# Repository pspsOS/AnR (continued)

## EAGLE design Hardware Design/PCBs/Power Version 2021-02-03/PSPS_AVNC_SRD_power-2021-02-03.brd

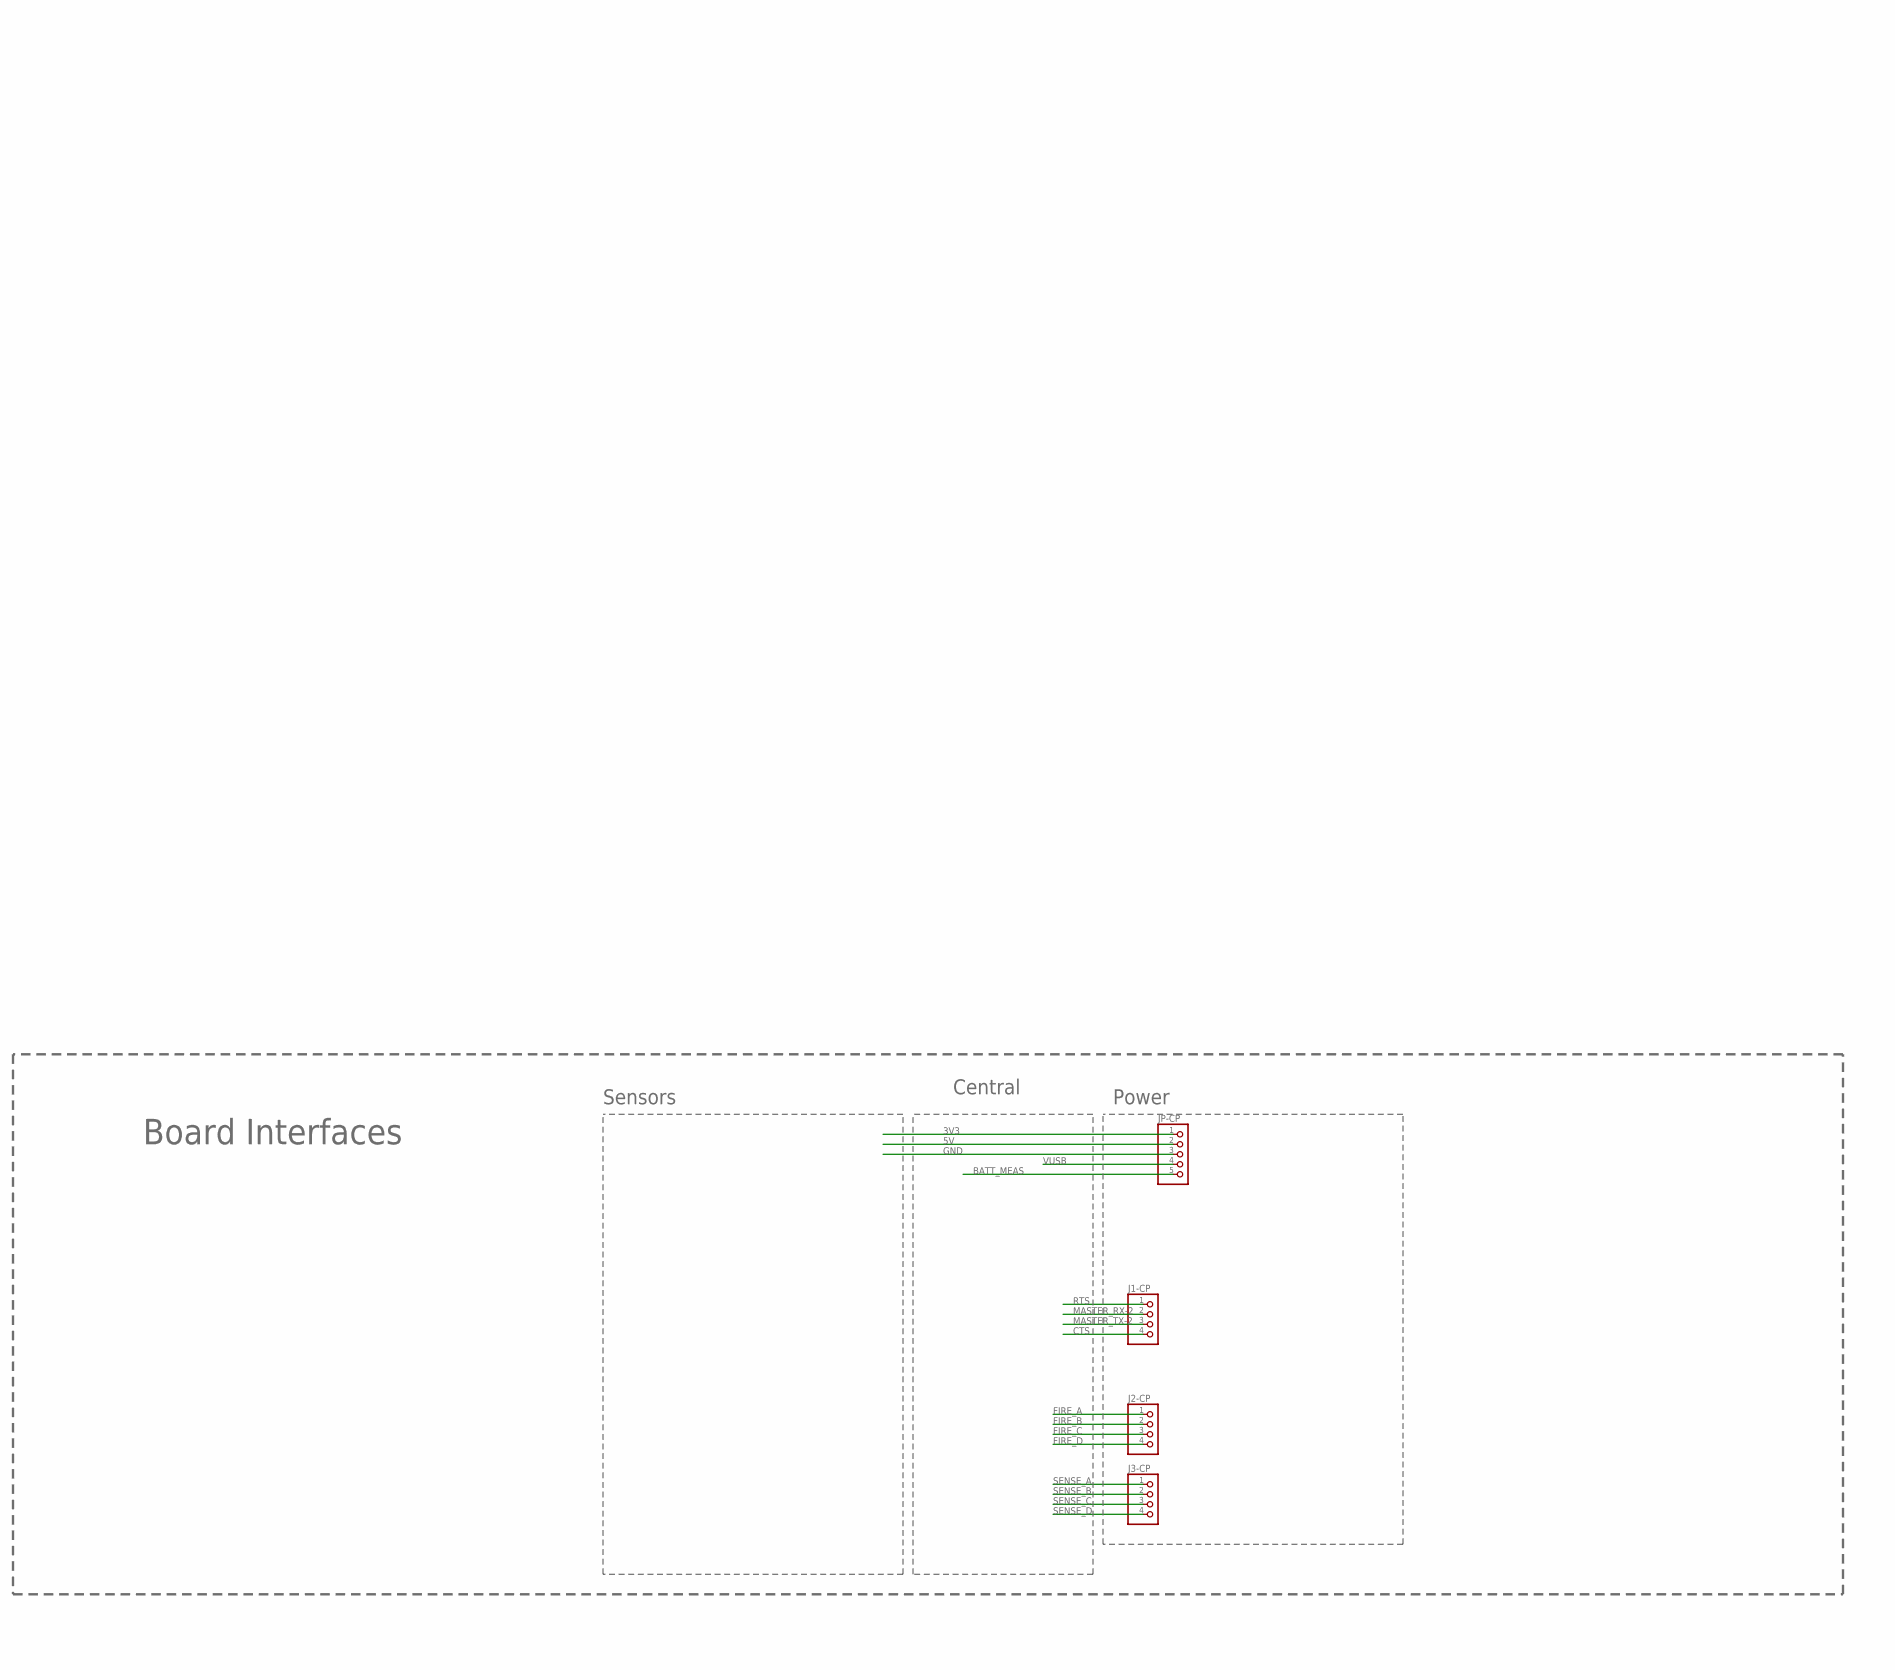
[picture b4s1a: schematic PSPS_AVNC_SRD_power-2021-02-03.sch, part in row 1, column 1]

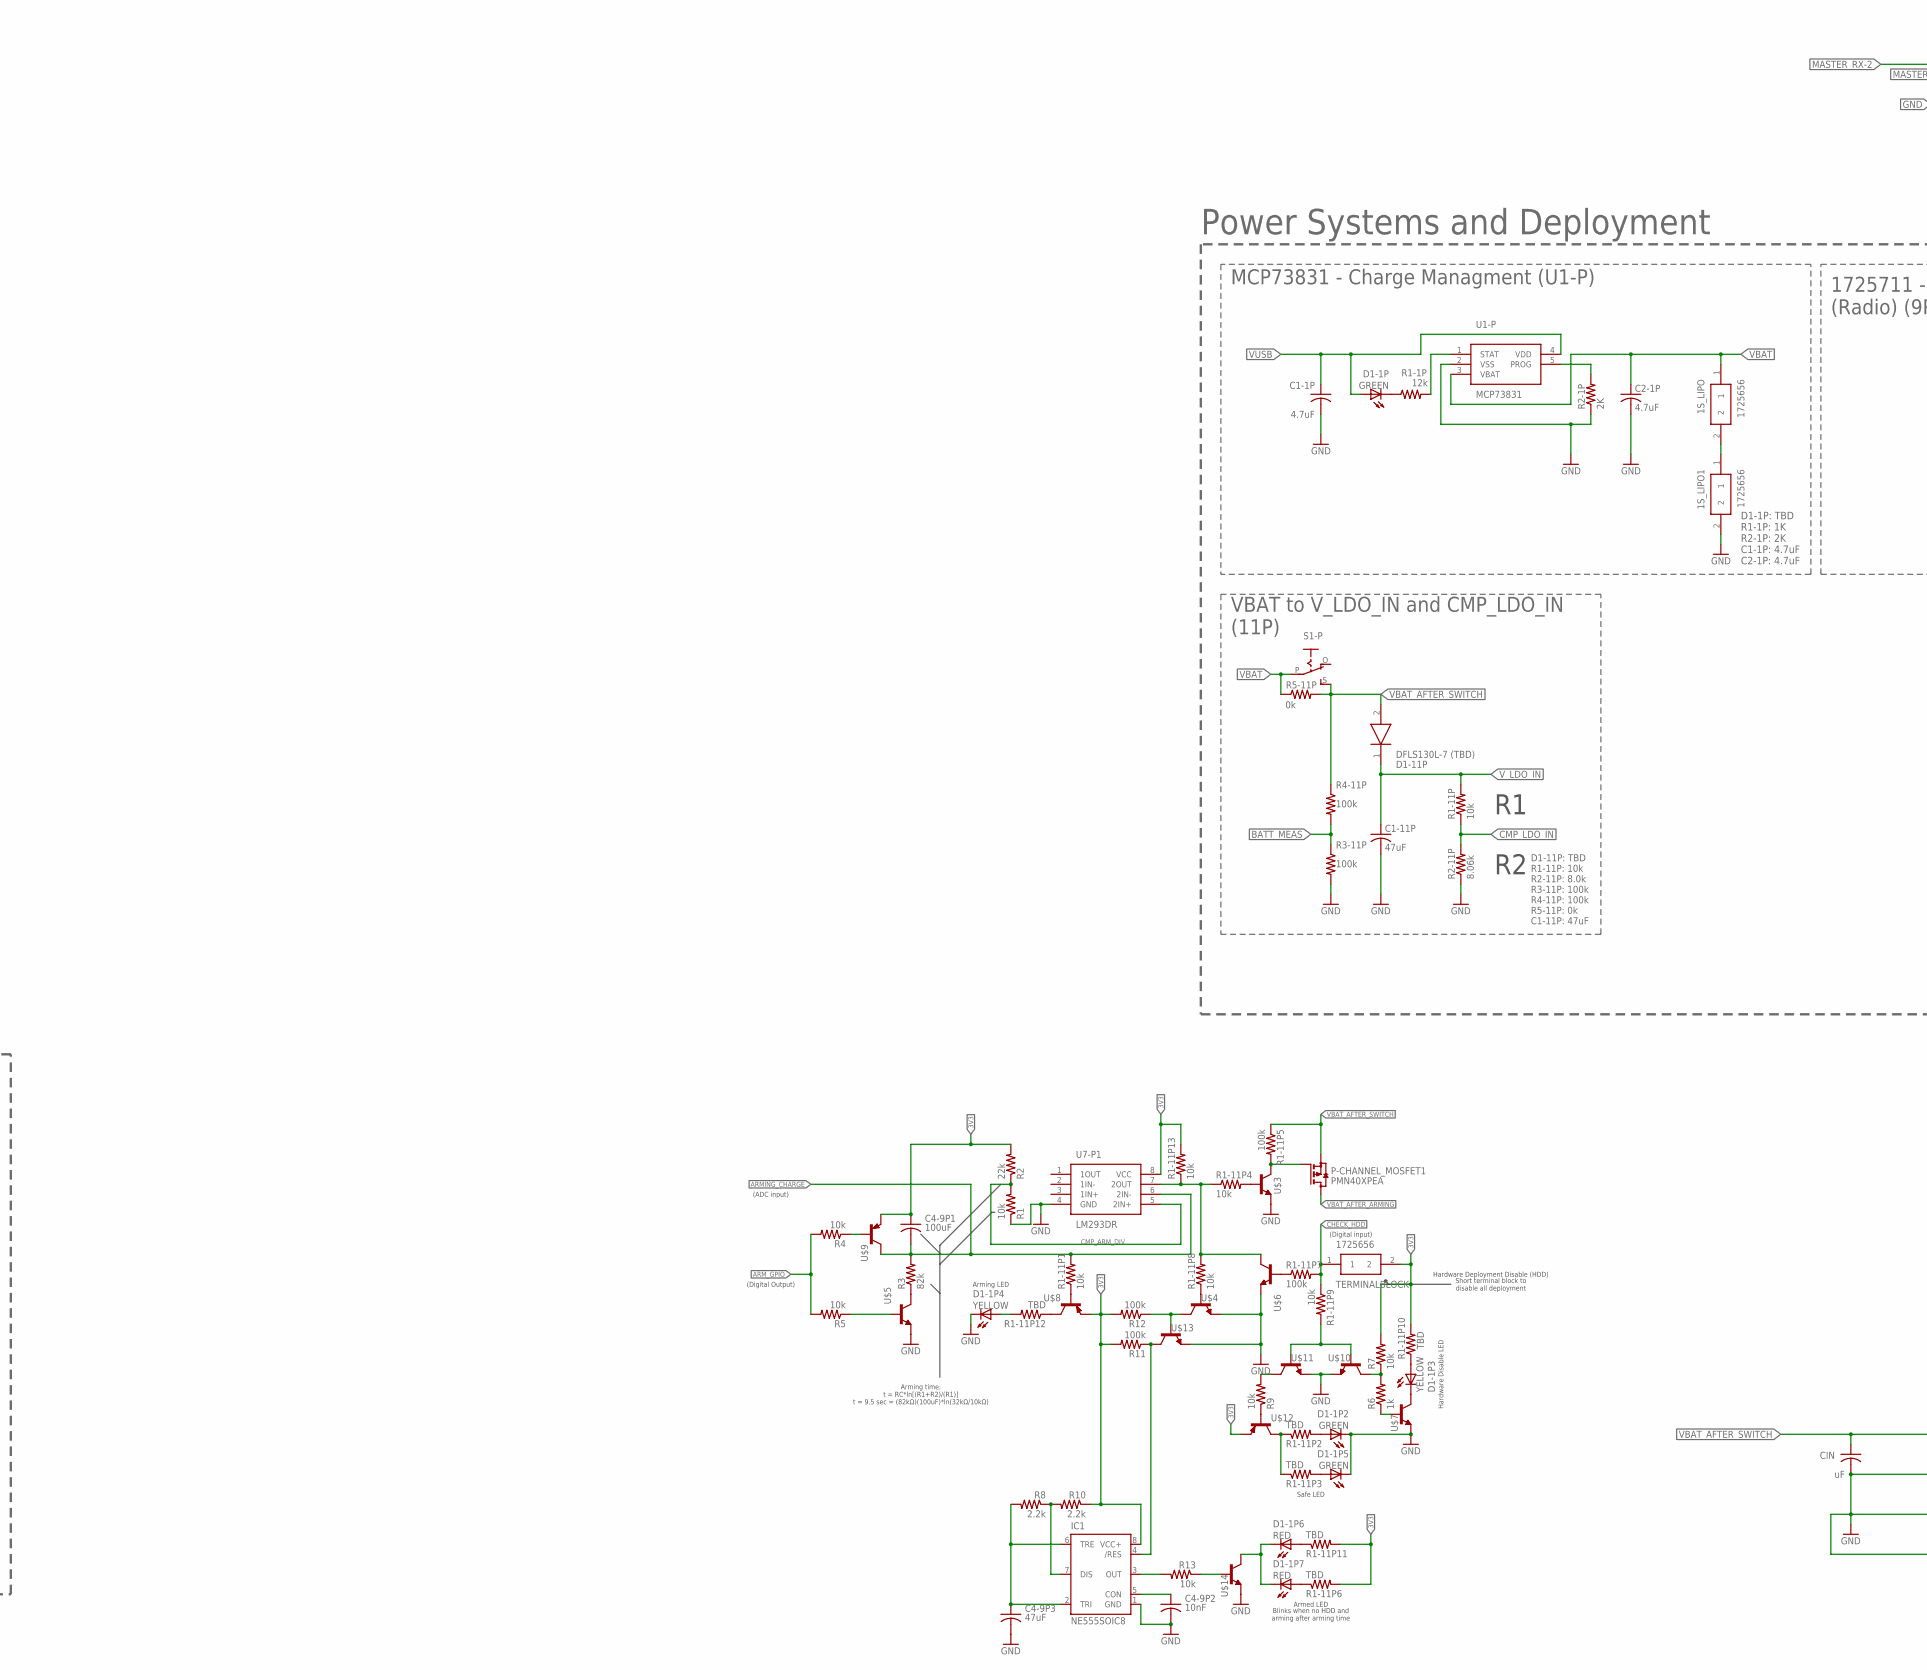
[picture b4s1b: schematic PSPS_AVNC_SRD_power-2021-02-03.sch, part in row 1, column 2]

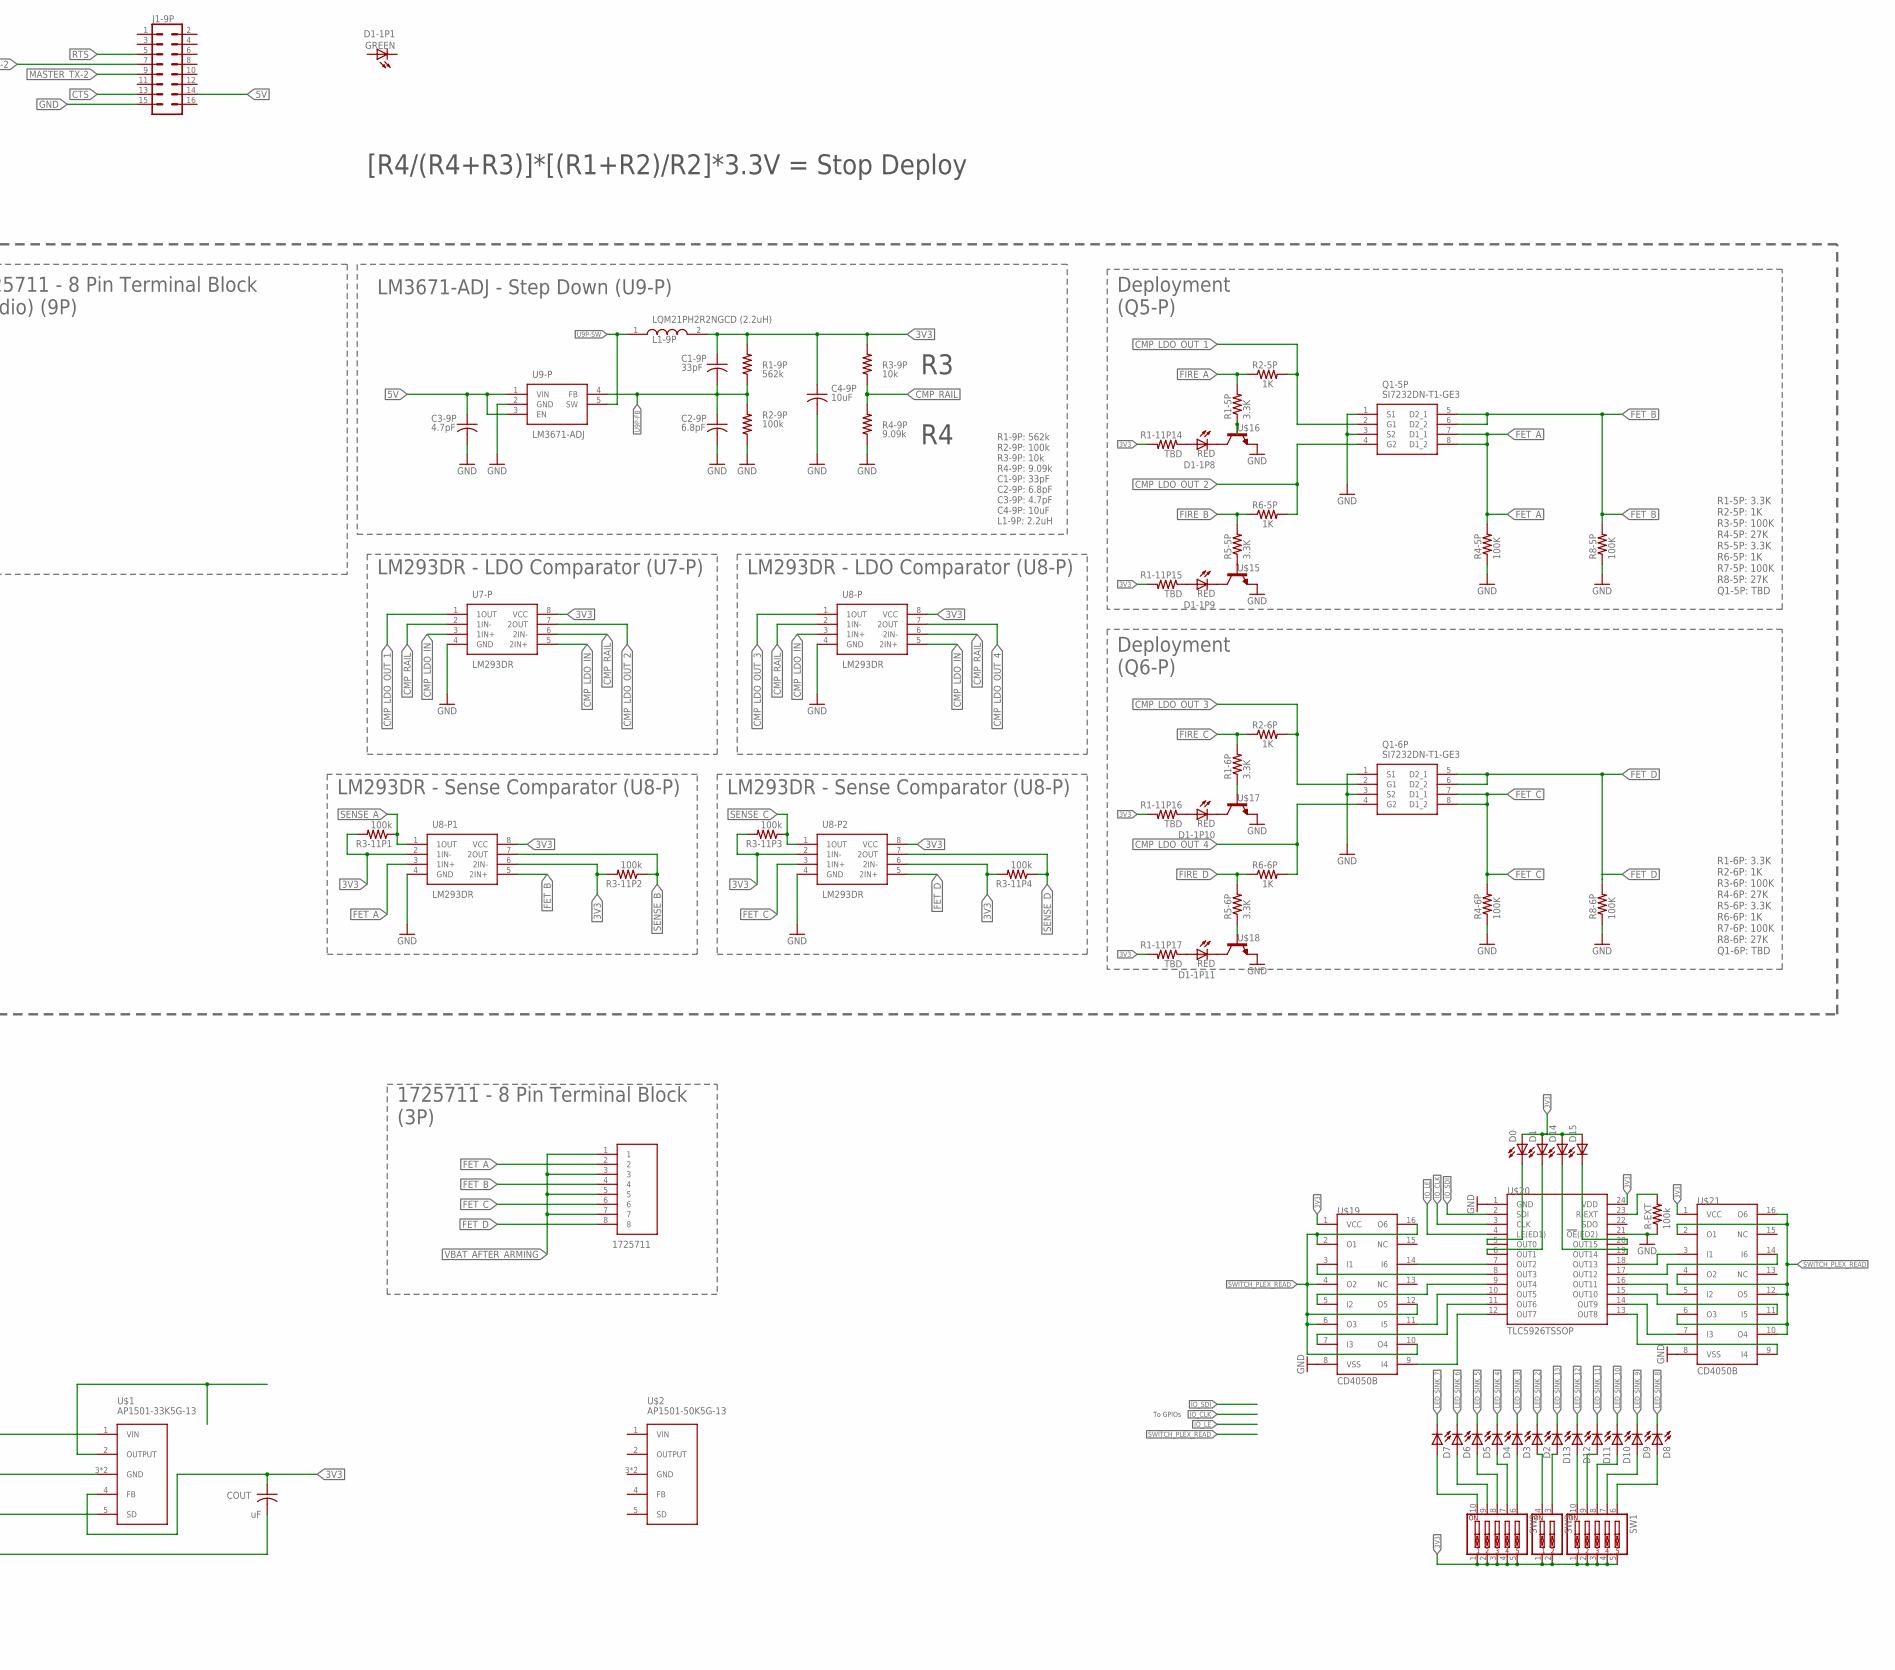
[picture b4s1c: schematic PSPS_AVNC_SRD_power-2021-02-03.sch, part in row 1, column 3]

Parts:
1S_LIPO, 1S_LIPO1: 1725656
C1-1P, C2-1P: 4.7uF; C0805
C1-9P: 33pF; C0805
C1-11P, C4-9P3: 47uF; C0805
C2-9P: 6.8pF; C0805
C3-9P: 4.7pF; C0805
C4-9P: 10uF; C0805
C4-9P1: 100uF; C0805
C4-9P2: 10nF; C0805
CIN: uF; C0805
COUT: uF; C0805
D0, D1, D2, D3, D4, D5, D6, D7, D8, D9, D10, D11, D12, D13, D14, D15: LEDCHIPLED_0805; CHIPLED_0805
D1-1P, D1-1P1, D1-1P2, D1-1P5: GREEN; CHIPLED_0805
D1-1P3, D1-1P4: YELLOW; CHIPLED_0805
D1-1P6, D1-1P7, D1-1P8, D1-1P9, D1-1P10, D1-1P11: RED; CHIPLED_0805
D1-11P: DFLS130L-7 (TBD); POWERDI_123
IC1: NE555SOIC8; SOIC127P599X175-8
J1-9P: CONN_08X2; 2X8
J1-CP, J2-CP, J3-CP: PINHD-1X4; 1X04
J2-P: 1725711
JP-CP: PINHD-1X5; 1X05
L1-9P: LQM21PH2R2NGCD (2.2uH); INDC2012X100N
P-CHANNEL_MOSFET1: PMN40XPEA
Q1-5P, Q1-6P: SI7232DN-T1-GE3; POWERPAK-1212-8
R1, R1-11P, R1-11P1, R1-11P4, R1-11P8, R1-11P9, R1-11P13, R3-9P, R4, R5, R7, R9, R13: 10k; R0805
R1-1P: 12k; R0805
R1-5P, R1-6P, R5-5P, R5-6P: 3.3K; M0805
R1-9P: 562k; R0805
R1-11P2, R1-11P3, R1-11P6, R1-11P10, R1-11P11, R1-11P12, R1-11P14, R1-11P15, R1-11P16, R1-11P17: TBD; R0805
R1-11P5, R1-11P7, R2-9P, R3-11P, R3-11P1, R3-11P2, R3-11P3, R3-11P4, R4-11P, R11, R12: 100k; R0805
R2: 22k; R0805
R2-1P: 2K; R0805
R2-5P, R2-6P, R6-5P, R6-6P: 1K; M0805
R2-11P: 8.06k; R0805
R3: 82k; R0805
R4-5P, R4-6P, R8-5P, R8-6P: 100K; M0805
R4-9P: 9.09k; R0805
R5-11P: 0k; R0805
R6: 1k; R0805
R8, R10: 2.2k; R0805
R-EXT: 100k; R0805
S1-P: EG1218S; EG1218
SW1, SW2: SW_DIP-5; EDG-05
SW3: SW_DIP-2; EDG-02
TERMINALBLOCK: 1725656
U1-P: MCP73831; SOT95P270X145-5N
U7-P, U7-P1, U8-P, U8-P1, U8-P2: LM293DR; SOIC127P600X175-8N
U9-P: LM3671-ADJ; SOT95P280X145-5N
U$1: AP1501-33K5G-13; TO185P1524X485-6N
U$2: AP1501-50K5G-13; TO185P1524X485-6N
U$3, U$4, U$5, U$6, U$7, U$10, U$11, U$13, U$14, U$15, U$16, U$17, U$18: NPN_TRANSISTOR; SOT23
U$8, U$9, U$12: PNP_TRANSISTOR; SOT23
U$19, U$21: CD4050B; SOIC127P600X175-16N
U$20: TLC5926TSSOP; SOP65P640X120-24N

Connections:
3V3: C1-9P.1, C4-9P.1, C4-9P1.1, COUT.1, D0.A, D1.A, D14.A, D15.A, IC1.8 (VCC+), JP-CP.1, L1-9P.2, R1-9P.2, R1-11P6.2, R1-11P10.2, R1-11P11.2, R1-11P13.2, R1-11P14.2, R1-11P15.2, R1-11P16.2, R1-11P17.2, R2.2, R3-9P.2, R3-11P1.2, R3-11P2.2, R3-11P3.2, R3-11P4.2, R7.2, R10.1, R11.2, R12.2, SW1.1, SW1.2, SW1.3, SW1.4, SW1.5, SW2.1, SW2.2, SW2.3, SW2.4, SW2.5, SW3.1, SW3.2, TERMINALBLOCK.2, U7-P.8 (VCC), U7-P1.8 (VCC), U8-P.8 (VCC), U8-P1.2 (1IN-), U8-P1.6 (2IN-), U8-P1.8 (VCC), U8-P2.2 (1IN-), U8-P2.6 (2IN-), U8-P2.8 (VCC), U$1.4 (FB), U$8.2 (E), U$9.2 (E), U$12.2 (E), U$19.1 (VCC), U$20.24 (VDD), U$21.1 (VCC)
5V: C3-9P.1, J1-9P.14, JP-CP.2, U9-P.1 (VIN), U9-P.3 (EN)
ARMING_CHARGE: C4-9P1.2, R1-11P1.2, R3.2, U7-P1.6 (2IN-), U$9.3 (C)
ARM_GPIO: R4.2, R5.2
BATT_MEAS: JP-CP.5, R3-11P.1, R4-11P.2
CHECK_HDD: R1-11P7.2, R1-11P9.1, TERMINALBLOCK.1
CMP_ARM_DIV: R1.2, R2.1, U7-P1.5 (2IN+)
CMP_LDO_IN: R1-11P.1, R2-11P.2, U7-P.3 (1IN+), U7-P.5 (2IN+), U8-P.3 (1IN+), U8-P.5 (2IN+)
CMP_LDO_OUT_1: Q1-5P.2 (G1), R2-5P.2, U7-P.1 (1OUT)
CMP_LDO_OUT_2: Q1-5P.4 (G2), R6-5P.2, U7-P.7 (2OUT)
CMP_LDO_OUT_3: Q1-6P.2 (G1), R2-6P.2, U8-P.1 (1OUT)
CMP_LDO_OUT_4: Q1-6P.4 (G2), R6-6P.2, U8-P.7 (2OUT)
CMP_RAIL: R3-9P.1, R4-9P.2, U7-P.2 (1IN-), U7-P.6 (2IN-), U8-P.2 (1IN-), U8-P.6 (2IN-)
CTS: J1-9P.13, J1-CP.4
D1-1P_R1-1P: D1-1P.C, R1-1P.1
FET_A: J2-P.2, Q1-5P.7 (D1_1), Q1-5P.8 (D1_2), R4-5P.2, U8-P1.3 (1IN+)
FET_B: J2-P.4, Q1-5P.5 (D2_1), Q1-5P.6 (D2_2), R8-5P.2, U8-P1.5 (2IN+)
FET_C: J2-P.6, Q1-6P.7 (D1_1), Q1-6P.8 (D1_2), R4-6P.2, U8-P2.3 (1IN+)
FET_D: J2-P.8, Q1-6P.5 (D2_1), Q1-6P.6 (D2_2), R8-6P.2, U8-P2.5 (2IN+)
FIRE_A: J2-CP.1, R1-5P.2, R2-5P.1
FIRE_B: J2-CP.2, R5-5P.2, R6-5P.1
FIRE_C: J2-CP.3, R1-6P.2, R2-6P.1
FIRE_D: J2-CP.4, R5-6P.2, R6-6P.1
GND: 1S_LIPO1.2, C1-1P.2, C1-11P.2, C2-1P.2, C2-9P.2, C3-9P.2, C4-9P.2, C4-9P2.2, C4-9P3.2, CIN.2, COUT.2, D1-1P2.C, D1-1P4.C, D1-1P5.C, IC1.1 (GND), J1-9P.15, JP-CP.3, Q1-5P.1 (S1), Q1-5P.3 (S2), Q1-6P.1 (S1), Q1-6P.3 (S2), R1.1, R2-1P.1, R2-9P.1, R2-11P.1, R3-11P.2, R4-5P.1, R4-6P.1, R4-9P.1, R8-5P.1, R8-6P.1, R-EXT.1, U1-P.2 (VSS), U7-P.4 (GND), U7-P1.4 (GND), U8-P.4 (GND), U8-P1.4 (GND), U8-P2.4 (GND), U9-P.2 (GND), U$1.3 (GND), U$1.5 (SD), U$1.6 (GND), U$3.3 (E), U$4.3 (E), U$5.3 (E), U$6.3 (E), U$7.3 (E), U$10.3 (E), U$11.3 (E), U$13.3 (E), U$14.3 (E), U$15.3 (E), U$16.3 (E), U$17.3 (E), U$18.3 (E), U$19.8 (VSS), U$20.1 (GND), U$20.21 (!OE!(ED2)), U$21.8 (VSS)
IO_CLK: U$20.3 (CLK)
IO_LE: U$20.4 (LE(ED1))
IO_SDI: U$20.2 (SDI)
LED_SINK_0: D0.C, U$20.5 (OUT0)
LED_SINK_1: D1.C, U$20.6 (OUT1)
LED_SINK_2: D2.C, U$19.14 (I6), U$20.7 (OUT2)
LED_SINK_3: D3.C, U$19.3 (I1), U$20.8 (OUT3)
LED_SINK_4: D4.C, U$19.5 (I2), U$20.9 (OUT4)
LED_SINK_5: D5.C, U$19.11 (I5), U$20.10 (OUT5)
LED_SINK_6: D6.C, U$19.7 (I3), U$20.11 (OUT6)
LED_SINK_7: D7.C, U$19.9 (I4), U$20.12 (OUT7)
LED_SINK_8: D8.C, U$20.13 (OUT8), U$21.9 (I4)
LED_SINK_9: D9.C, U$20.14 (OUT9), U$21.7 (I3)
LED_SINK_10: D10.C, U$20.15 (OUT10), U$21.11 (I5)
LED_SINK_11: D11.C, U$20.16 (OUT11), U$21.5 (I2)
LED_SINK_12: D12.C, U$20.17 (OUT12), U$21.14 (I6)
LED_SINK_13: D13.C, U$20.18 (OUT13), U$21.3 (I1)
LED_SINK_14: D14.C, U$20.19 (OUT14)
LED_SINK_15: D15.C, U$20.20 (OUT15)
MASTER_RX-2: J1-9P.7, J1-CP.2
MASTER_TX-2: J1-9P.9, J1-CP.3
unnamed: 1S_LIPO.2, 1S_LIPO1.1
unnamed: R1-11P8.1, U$4.1 (B)
unnamed: R1-11P1.1, U$8.1 (B)
unnamed: D1-1P3.C, U$7.2 (C)
unnamed: R6.2, R7.1, U$10.2 (C)
unnamed: R6.1, U$7.1 (B)
unnamed: P-CHANNEL_MOSFET1.3 (G), R1-11P5.2, U$3.2 (C)
unnamed: R1-11P4.2, U$3.1 (B)
unnamed: R1-11P4.1, R1-11P8.2, R1-11P13.1, U7-P1.7 (2OUT), U$6.2 (C)
unnamed: R5.1, U$5.1 (B)
unnamed: R1-11P7.1, U$6.1 (B)
unnamed: R1-11P2.1, R1-11P3.1, U$12.3 (C)
unnamed: R1-11P9.2, U$10.1 (B), U$11.1 (B)
unnamed: R3.1, U$5.2 (C)
unnamed: D1-1P2.A, R1-11P2.2
unnamed: D1-1P3.A, R1-11P10.1
unnamed: R12.1, U$4.2 (C), U$13.1 (B)
unnamed: D1-1P6.A, R1-11P11.1
unnamed: R9.1, U$12.1 (B)
unnamed: R1-11P12.1, U$8.3 (C)
unnamed: D1-1P4.A, R1-11P12.2
unnamed: R9.2, U$11.2 (C)
unnamed: R4.1, U$9.1 (B)
unnamed: D1-1P5.A, R1-11P3.2
unnamed: IC1.4 (/RES), R11.1, U$13.2 (C)
unnamed: R13.1, U$14.1 (B)
unnamed: C4-9P2.1, IC1.5 (CON)
unnamed: C4-9P3.1, IC1.2 (TRI), IC1.6 (TRE), R8.2
unnamed: IC1.7 (DIS), R8.1, R10.2
unnamed: IC1.3 (OUT), R13.2
unnamed: D1-1P7.A, R1-11P6.1
unnamed: D1-1P6.C, D1-1P7.C, U$14.2 (C)
unnamed: R5-5P.1, U$15.1 (B)
unnamed: D1-1P8.C, U$16.2 (C)
unnamed: D1-1P9.A, R1-11P15.1
unnamed: D1-1P9.C, U$15.2 (C)
unnamed: D1-1P8.A, R1-11P14.1
unnamed: R1-5P.1, U$16.1 (B)
unnamed: R1-6P.1, U$17.1 (B)
unnamed: R5-6P.1, U$18.1 (B)
unnamed: D1-1P10.C, U$17.2 (C)
unnamed: D1-1P10.A, R1-11P16.1
unnamed: D1-1P11.C, U$18.2 (C)
unnamed: D1-1P11.A, R1-11P17.1
unnamed: D7.A, SW2.10
unnamed: R-EXT.2, U$20.23 (R-EXT)
unnamed: D3.A, SW2.6
unnamed: D4.A, SW2.7
unnamed: D5.A, SW2.8
unnamed: D6.A, SW2.9
unnamed: D2.A, SW3.4
unnamed: D12.A, SW1.10
unnamed: D11.A, SW1.9
unnamed: D10.A, SW1.8
unnamed: D9.A, SW1.7
unnamed: D8.A, SW1.6
unnamed: D13.A, SW3.3
RTS: J1-9P.5, J1-CP.1
SENSE_A: J3-CP.1, R3-11P1.1, U8-P1.1 (1OUT)
SENSE_B: J3-CP.2, R3-11P2.1, U8-P1.7 (2OUT)
SENSE_C: J3-CP.3, R3-11P3.1, U8-P2.1 (1OUT)
SENSE_D: J3-CP.4, R3-11P4.1, U8-P2.7 (2OUT)
SWITCH_PLEX_READ: U$19.2 (O1), U$19.4 (O2), U$19.6 (O3), U$19.10 (O4), U$19.12 (O5), U$19.16 (O6), U$21.2 (O1), U$21.4 (O2), U$21.6 (O3), U$21.10 (O4), U$21.12 (O5), U$21.16 (O6)
U1P-PROG: R2-1P.2, U1-P.5 (PROG)
U1P-STAT: R1-1P.2, U1-P.1 (STAT)
U9P-FB: C1-9P.2, C2-9P.1, R1-9P.1, R2-9P.2, U9-P.4 (FB)
U9P-SW: L1-9P.1, U9-P.5 (SW)
VBAT: 1S_LIPO.1, C2-1P.1, R5-11P.1, S1-P.P, U1-P.3 (VBAT)
VBAT_AFTER_ARMING: J2-P.1, J2-P.3, J2-P.5, J2-P.7, P-CHANNEL_MOSFET1.1 (D), P-CHANNEL_MOSFET1.2 (D), P-CHANNEL_MOSFET1.5 (D), P-CHANNEL_MOSFET1.6 (D)
VBAT_AFTER_SWITCH: CIN.1, D1-11P.2 (A), P-CHANNEL_MOSFET1.4 (S), R1-11P5.1, R4-11P.1, R5-11P.2, S1-P.S, U$1.1 (VIN)
VUSB: C1-1P.1, D1-1P.A, JP-CP.4, U1-P.4 (VDD)
V_LDO_IN: C1-11P.1, D1-11P.1 (K), R1-11P.2

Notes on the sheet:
Power Systems and Deployment
Deployment (Q5-P)
R1-5P: 3.3K R2-5P: 1K R3-5P: 100K R4-5P: 27K R5-5P: 3.3K R6-5P: 1K R7-5P: 100K R8-5P: 27K Q1-5P: TBD
1725711 - 8 Pin Terminal Block (3P)
MCP73831 - Charge Managment (U1-P)
D1-1P: TBD R1-1P: 1K R2-1P: 2K C1-1P: 4.7uF C2-1P: 4.7uF
LM3671-ADJ - Step Down (U9-P)
R1-9P: 562k R2-9P: 100k R3-9P: 10k R4-9P: 9.09k C1-9P: 33pF C2-9P: 6.8pF C3-9P: 4.7pF C4-9P: 10uF L1-9P: 2.2uH
LM293DR - LDO Comparator (U7-P)
VBAT to V_LDO_IN and CMP_LDO_IN (11P)
D1-11P: TBD R1-11P: 10k R2-11P: 8.0k R3-11P: 100k R4-11P: 100k R5-11P: 0k C1-11P: 47uF
Deployment (Q6-P)
R1-6P: 3.3K R2-6P: 1K R3-6P: 100K R4-6P: 27K R5-6P: 3.3K R6-6P: 1K R7-6P: 100K R8-6P: 27K Q1-6P: TBD
LM293DR - LDO Comparator (U8-P)
1725711 - 8 Pin Terminal Block (Radio) (9P)
Central
Power
Sensors
Board Interfaces
[R4/(R4+R3)]*[(R1+R2)/R2]*3.3V = Stop Deploy
LM293DR - Sense Comparator (U8-P)
(Digital Output)
Hardware Disable LED
Arming LED
Armed LED
Blinks when no HDD and arming after arming time
Hardware Deployment Disable (HDD)
Short terminal block to disable all deployment
Arming time: t = RC*ln[(R1+R2)/(R1)] t ≈ 9.5 sec = (82kΩ)(100uF)*ln(32kΩ/10kΩ)
(ADC input)
(Digital input)
Safe LED
To GPIOs

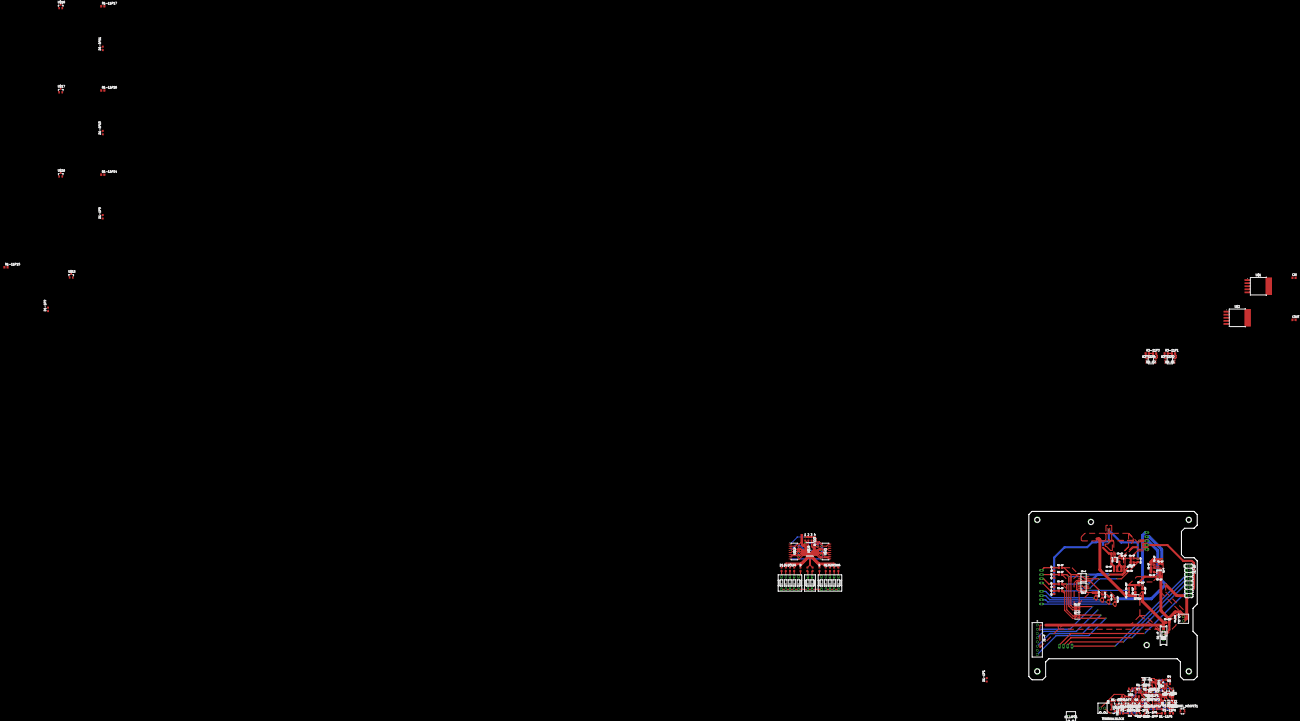
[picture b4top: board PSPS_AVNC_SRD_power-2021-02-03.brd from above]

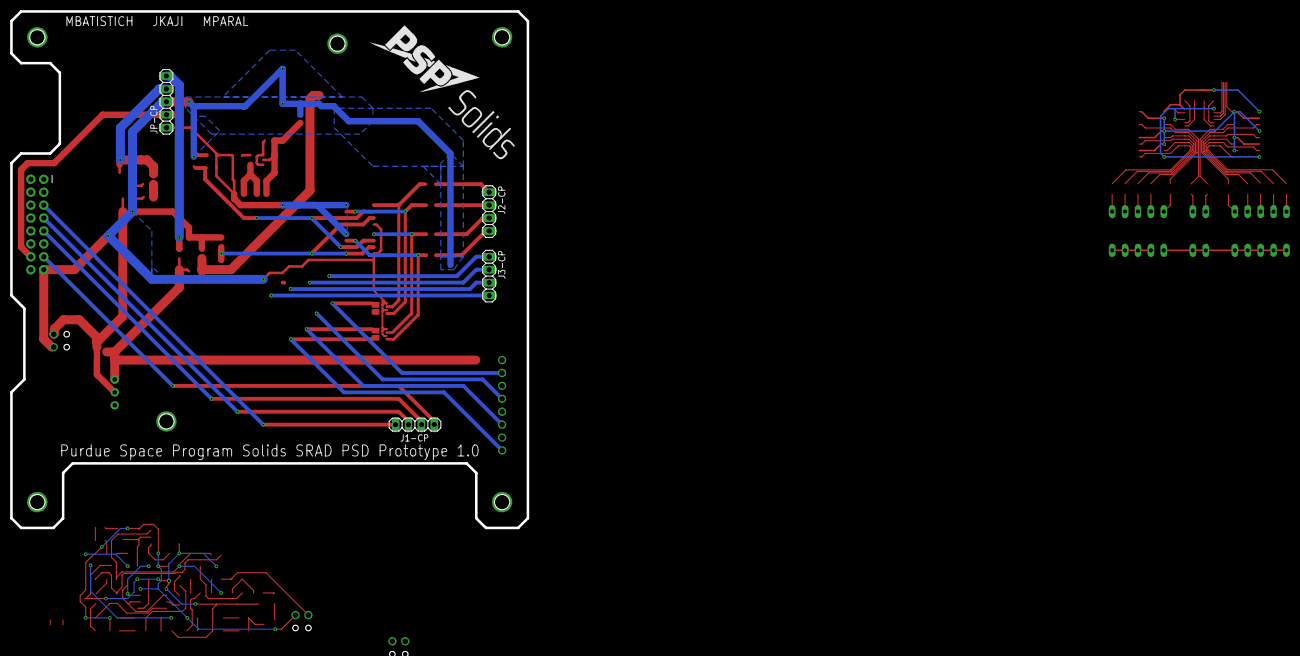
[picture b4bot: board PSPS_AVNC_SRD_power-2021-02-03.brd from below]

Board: 2 copper layers, 145 parts (4 on the bottom side), 114 nets.
